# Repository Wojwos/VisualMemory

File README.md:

# VisualMemory
### Opis założeń.
Projekt ma być odwzorowaniem testu na pamięc wizualną człowieka.Układ będzie złożony z przycisków 6x6 z podświetlaniem LED oraz wyświetlacza LCD, wyświetlający wynik testu. Inspiracją jest test, który można znaleźć na stronie www.humanbenchmark.com.

### Analiza zadania - wybór elementów elektronicznych i narzędzi użytych do realizacji projektu.

Podstawowe elementy jakie muszą znaleźć się w układzie:
- mikroprocesor
- wyświetlacz
- 36 przycisków
- zasilacz
- diody LED

**Diody** - wybrany został pasek LED ws2812b, ponieważ jest bardzo prosty w użyciu, łatwy do podłączenia oraz do zaprogramowania. Ponadto na pasku LED znajduje się odpowiednio dużo diod LED, które można odcinać od reszty, a następnie za pomocą przewodów łączyć je z powrotem.

**Wyświetlacz** - dobrym wyborem był tutaj wyświetlacz LCD 16x2, ponieważ wyświetlanych informacji nie ma aż tak wiele, więc taka wielkość wystarczy.

**Zasilacz** - 5V zasilacz sieciowy jest tutaj odpowiedni ponieważ do poprawnego działania wybranych elementów potrzebne jest takie napięcie, możliwe byłoby również zasilanie przez USB, gdybyśmy chcieli użyć tego urządzenia jako kontroler MIDI, jednakże mogłoby to się wiązać z problemami w przypadku dużej ilości diod LED jednocześnie, ponieważ wymaga to dosyć sporej mocy.

**Przyciski** - tactile switch są tu w zupełności wystarczające przy założeniu, że projekt nie wymaga od nas dużej precyzji (tzn. szybkiego naciskania przycisków).

**Atmega328P-PU** - mikroprocesor AVR jest tutaj dobrym wyborem, ponieważ IDE, którym jest Arduino dostarcza nam proste w użyciu i intuicyjne biblioteki dla wybranych wcześniej komponentów. Dodatkowo warto zauważyć, że ilość pinów w tym procesorze idealnie pasuje do tego układu. Z pinów analogowych możemy korzystać jak z pinów cyfrowych po ustawieniu odpowiedniego trybu, dzięki temu nie trzeba się martwić o brak pinów cyfrowych

**Inne potrzebne elementy:**
- zestaw rezystorów
- diody 1N4007 - przydatne w klawiaturach matrycowych do eliminacji przekłamań
- zestaw kondensatorów
- potencjometr - dzięki niemu dostosować można kontrast na wyświetlaczu LCD
- płytka PCB
- kable
- perfboard (DOT PCB) - na nim będzie zbudowana cała konstrukcja (przyciski i diody LED)

### Specyfikacja wewnętrzna urządzenia.
**Schemat blokowy i ideowy urządzenia**

**Opis funkcji poszczególnych bloków układu, szczegółowy opis działania ważniejszych elementów układu**
Klawiatura matrycowa składa się z 36 przycisków, do każdego przycisku przyporządkowane dwie diody LED, ponieważ są gęsto rozstawione na pasku WS2812B. Klawiatura podłączona do reszty urządzenia z wyświetlaczem LCD, na którym wyświetlone są wszystkie informacje.

**Schemat montażowy obejmujący projekt płytki drukowanej, rozmieszczenie elementów na płytce oraz rozmieszczenie elementów urządzenia w obudowie**

**Lista elementów:**

Elementy na płytce PCB:
- Atmega328P-PU
- wyświetlacz LCD 16x2
- 2x rezystor 10k
- 6x dioda 1N4007
- 2x kondensator 100nF
- potencjometr
- gniazdo do zasilacza 5V

Elementy poza płytką (umieszczone na perfboardzie):
- 36x tactile switch
- 72x LED WS2812B

**Algorytm oprogramowania urządzenia, w tym schemat blokowy**

### Specyfikacja zewnętrzna urządzenia:
**Opis funkcji elementów sterujących urządzeniem**
Urządzeniem sterujemy wyłącznie za pomocą przycisków według instrukcji wyświetlanych na wyświetlaczu LCD. Przycisków łącznie jest 36. Czasami program wymaga od nas naciśnięcia odpowiednich przycisków, a czasem dowolnego w celu kontynuowania.

**Opis funkcji elementów wykonawczych (wyświetlacz, diody LED,**
przekaźniki)
Wyświetlacz informuje nas o wyniku, poziomie, oraz co należy zrobić.

**Opis reakcji oprogramowania na zdarzenia zewnętrzne**
Oprogramowanie odczytuje stan 36 przycisków podczas fazy zgadywania.

**Skrócona instrukcja obsługi urządzenia**
Urządzenie należy podłączyć do prądu, następnie wszystkie informacje zostaną wyświetlone na wyświetlaczu LCD takie jak:
- Naciśnij dowolny przycisk aby kontynuować
- Zapamiętaj podświetlone pole (mamy na to 3 sekundy)
- Zgadnij wszystkie pola (wyświetlona ilość pól odgadniętych i pól łącznie do odgadnięcia) - po wyświetleniu tej informacji naciskamy zapamiętane pola dopóki nie odgadniemy wszystkich lub stracimy wszystkie 3 życia
- Gratulacje! kontynuuj (musimy przycisnąć dowolny przycisk), kolejny poziom: ? - w zależności ile razy udało nam się odgadnąć wszystkie pola nie tracąc wszystkich żyć

**Opis złączy i/lub schematu okablowania**
Kable wychodzą ze skrzynki z układem scalonym do klawiatury (6 kabli do kolumn, 6 kabli do wierszy, 3 kable do diod LED)

**Opis montażu układu**
Układ scalony znajduje się w skrzynce z wbudowanym wyświetlaczem LCD, klawiatura oraz diody LED znajdują się na oddzielnym perfboardzie.

**Opis sposobu programowania układu**
Oprogramowanie zostało stworzone w Arduino IDE z wykorzystaniem bibliotek obsługujących klawiaturę matrycową, wyświetlacz LCD oraz diody LED ws2812b.

### Działanie

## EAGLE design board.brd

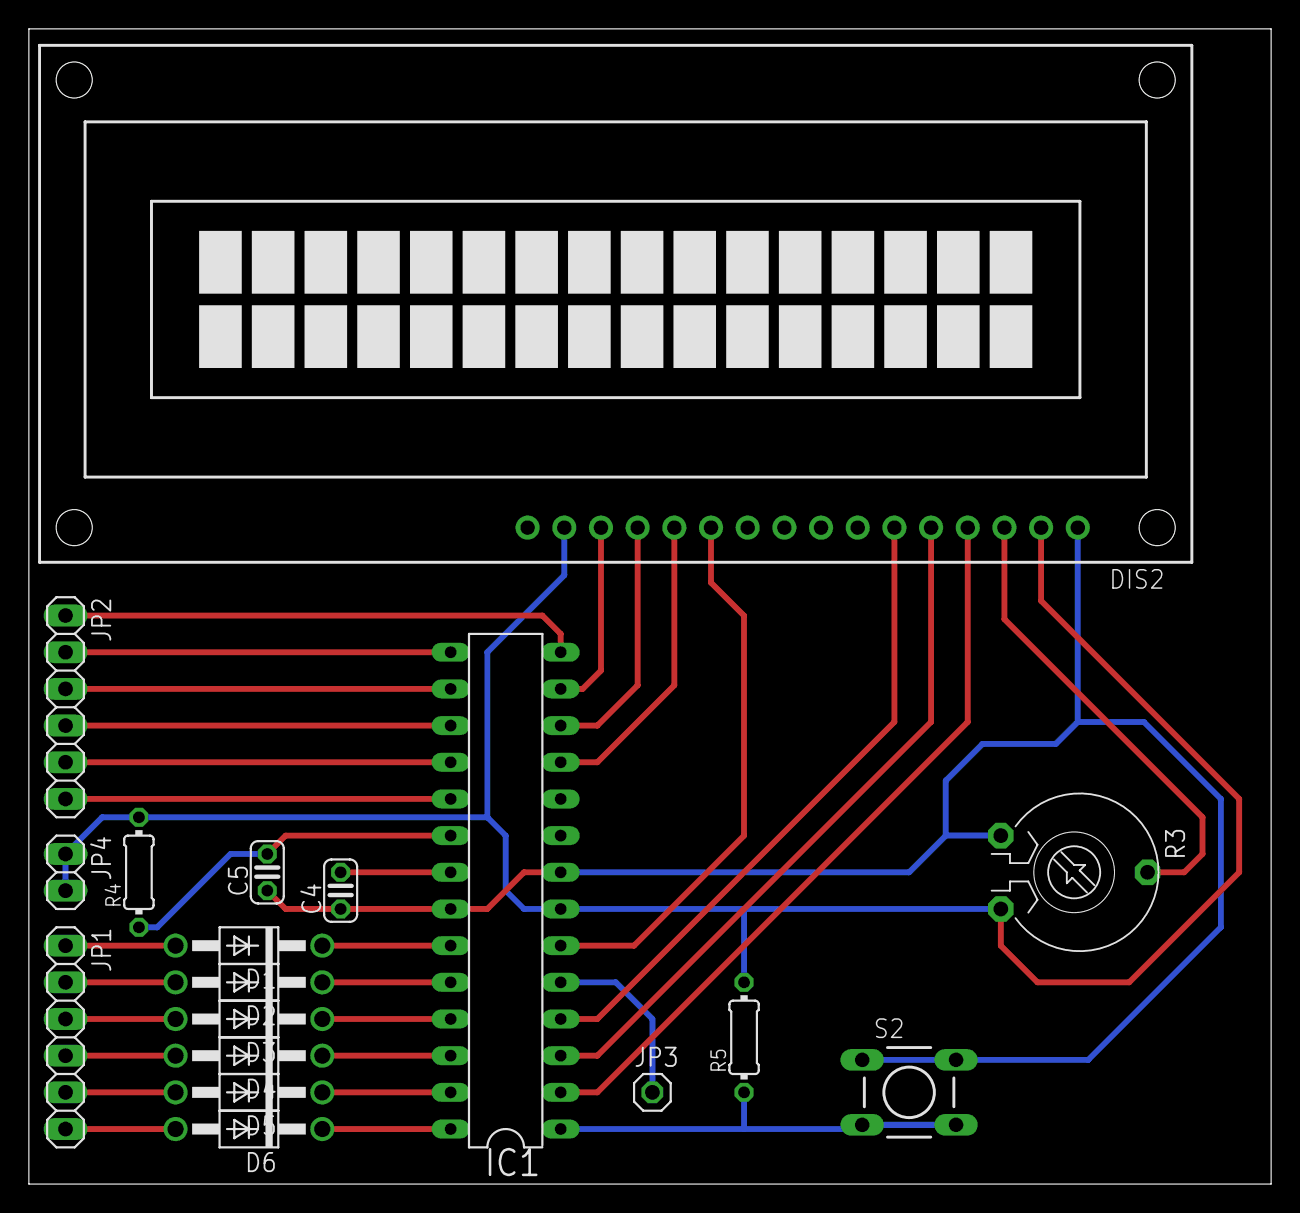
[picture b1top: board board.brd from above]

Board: 2 copper layers, 86.0 x 80.0 mm, 18 parts (0 on the bottom side), 32 nets.

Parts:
C4, C5: 100nF; C025-024X044
D1, D2, D3, D4, D5, D6: 1N4004; DO41-10
DIS2: TUXGR_16X2_R2
IC1: ATMEGA328-20P; DIL28-3
JP1, JP2: 1X06
JP3: 1X01
JP4: 1X02
R3: 10K; PT-10
R4, R5: 10K; 0204/7
S2: DTS-6

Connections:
GND: C4.1, C5.1, DIS2.1, IC1.8, IC1.22, R3.1, S2.1, S2.2
unnamed: D1.C, IC1.23
unnamed: D2.C, IC1.24
unnamed: DIS2.3, R3.3
unnamed: DIS2.6, IC1.4
unnamed: C5.2, IC1.20, R4.1
unnamed: DIS2.5, IC1.3
unnamed: IC1.5, JP3.1
unnamed: DIS2.11, IC1.6
unnamed: DIS2.12, IC1.11
unnamed: DIS2.13, IC1.12
unnamed: DIS2.14, IC1.13
unnamed: IC1.1, R5.1, S2.3, S2.4
unnamed: DIS2.4, IC1.2
unnamed: C4.2, IC1.21
unnamed: D3.C, IC1.25
unnamed: D4.C, IC1.26
unnamed: D5.C, IC1.27
unnamed: D6.C, IC1.28
unnamed: IC1.14, JP2.1
unnamed: IC1.15, JP2.2
unnamed: IC1.16, JP2.3
unnamed: IC1.17, JP2.4
unnamed: IC1.18, JP2.5
unnamed: IC1.19, JP2.6
unnamed: D1.A, JP1.1
unnamed: D2.A, JP1.2
unnamed: D3.A, JP1.3
unnamed: D4.A, JP1.4
unnamed: D5.A, JP1.5
unnamed: D6.A, JP1.6
unnamed: DIS2.2, DIS2.15, IC1.7, JP4.1, JP4.2, R3.2, R4.2, R5.2
